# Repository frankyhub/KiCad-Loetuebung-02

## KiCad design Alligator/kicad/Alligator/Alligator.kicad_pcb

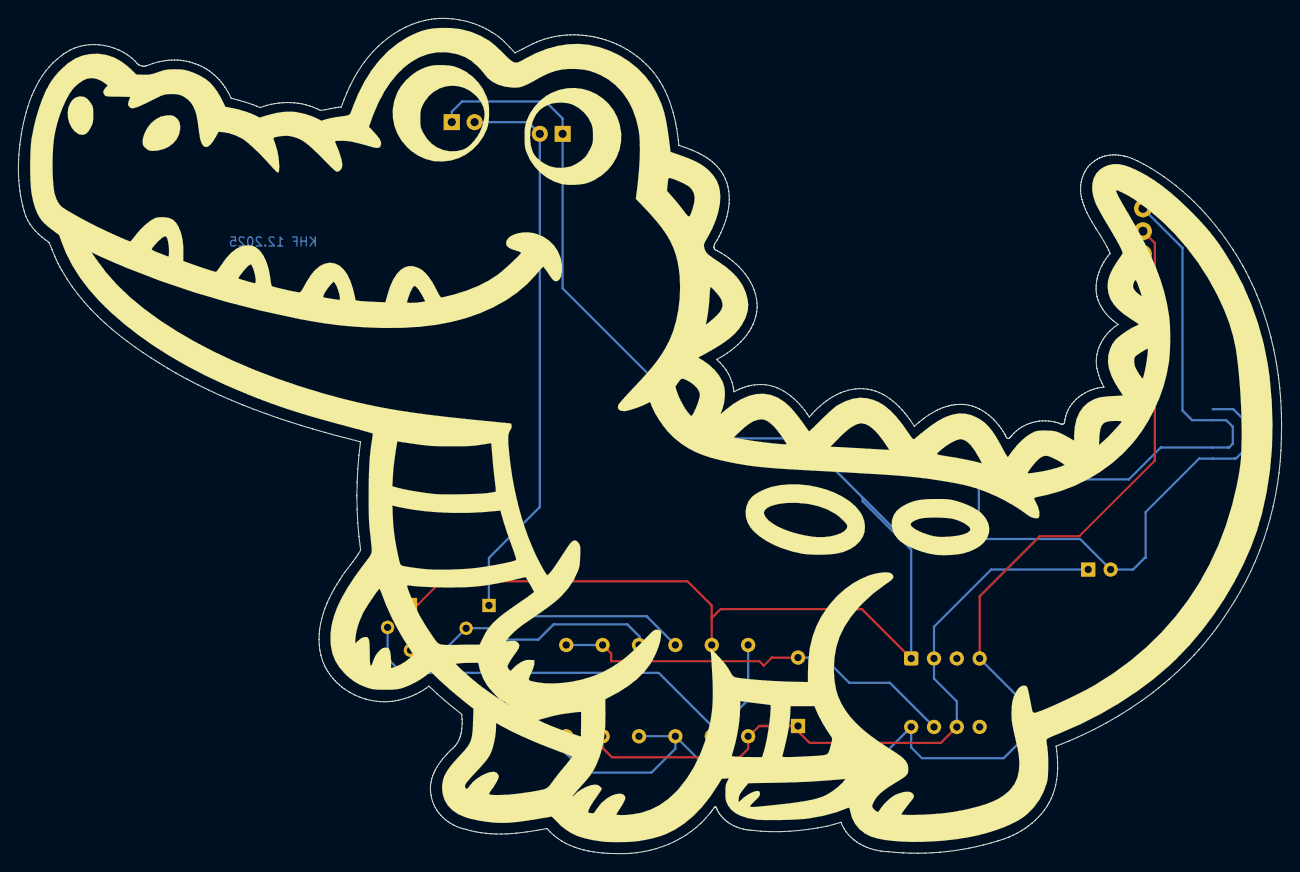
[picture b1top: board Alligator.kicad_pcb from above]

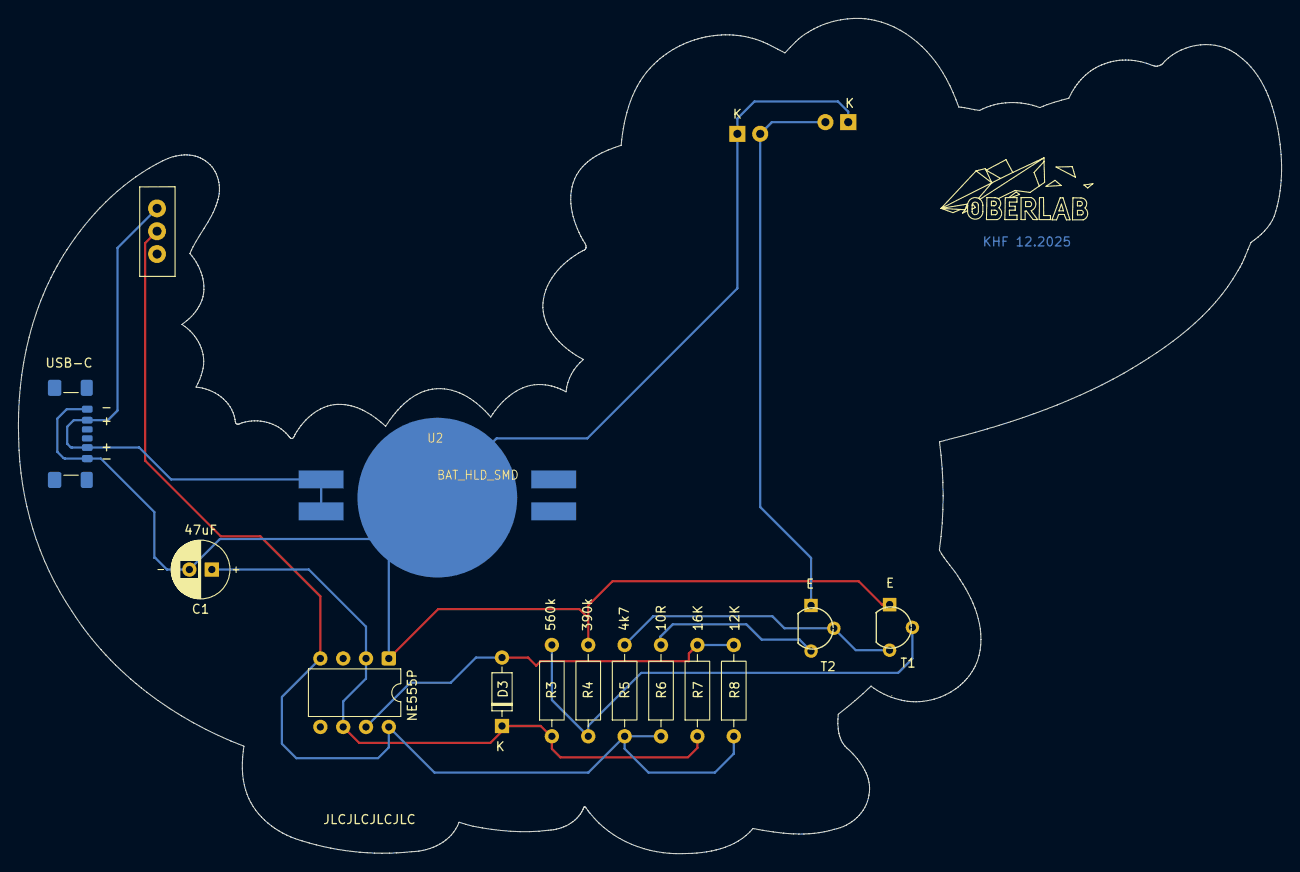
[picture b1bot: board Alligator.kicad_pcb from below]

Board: 2 copper layers, 140.6 x 93.0 mm, 16 parts (14 on the bottom side), 9 nets.

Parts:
C1: 47uF; C_Radial_D6.3mm_P2.50mm
D1, D2: LED; LED_D3.0mm
D3: 1N4148; 1N4147_P7.62mm_Horizontal
Q1, Q2: Q_NPN_EBC; TO-92L_Wide
R3: 560k; R_Axial_DIN0207_L6.3mm_D2.5mm_P10.16mm_Horizontal
R4: 390k; R_Axial_DIN0207_L6.3mm_D2.5mm_P10.16mm_Horizontal
R5: 4k7; R_Axial_DIN0207_L6.3mm_D2.5mm_P10.16mm_Horizontal
R6: 10R; R_Axial_DIN0207_L6.3mm_D2.5mm_P10.16mm_Horizontal
R7: 16K; R_Axial_DIN0207_L6.3mm_D2.5mm_P10.16mm_Horizontal
R8: 12K; R_Axial_DIN0207_L6.3mm_D2.5mm_P10.16mm_Horizontal
S1: Micro_Schalter; Micro_SchalterKHF
U1: NE555P; DIP-8_W7.62mm
U2: BAT_HLD_SMD; BAT-HLD-SMD-Blech
USB-C: USB_C_Receptacle_GCT_USB4135-GF-A_6P_TopMnt_Horiz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; USB_C_Receptacle_GCT_USB4135-GF-A_6P_TopMnt_Horizontal

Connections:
unnamed: D1.2 (A), D2.2 (A), Q2.1 (E)
unnamed: C1.2, D1.1 (K), D2.1 (K), Q1.1 (E), R4.2, U1.1 (GND), U2.2, USB-C.A12, USB-C.B12
unnamed: D3.2 (A), R7.2, R8.2, U1.7 (DIS)
unnamed: C1.1, D3.1 (K), R3.1, R7.1, U1.2 (TR), U1.6 (THR)
unnamed: Q1.2 (B), R3.2, R4.1
unnamed: Q1.3 (C), Q2.2 (B), R5.2
unnamed: Q2.3 (C), R6.2
unnamed: S1.1 (A), U2.1, USB-C.A9, USB-C.B9
unnamed: R5.1, R6.1, R8.1, S1.2 (E), U1.4 (R), U1.8 (VCC)

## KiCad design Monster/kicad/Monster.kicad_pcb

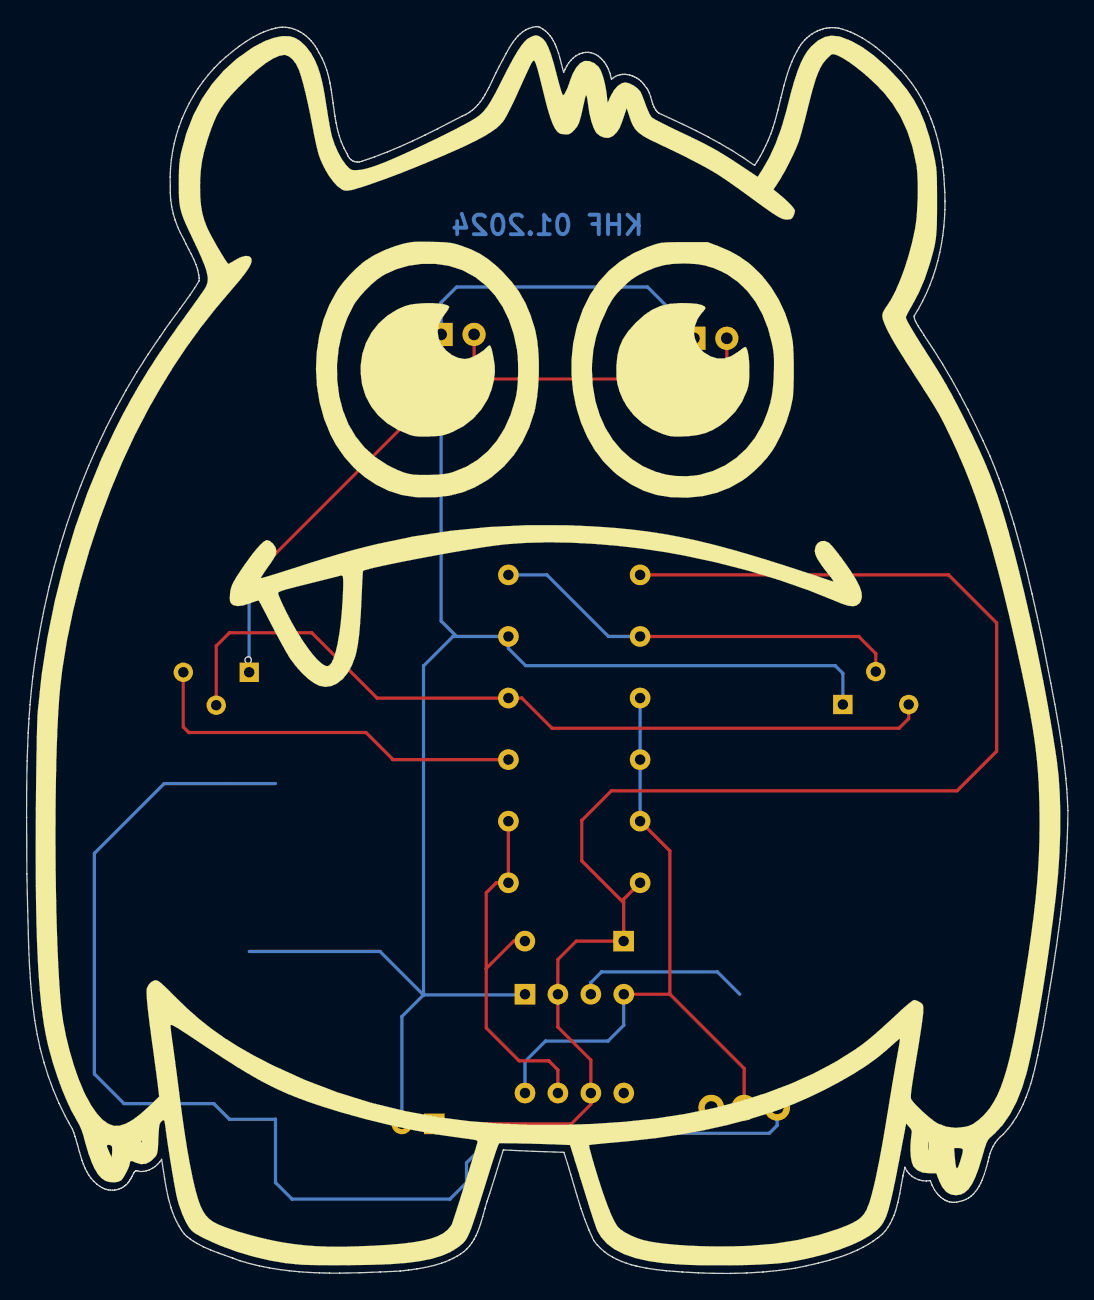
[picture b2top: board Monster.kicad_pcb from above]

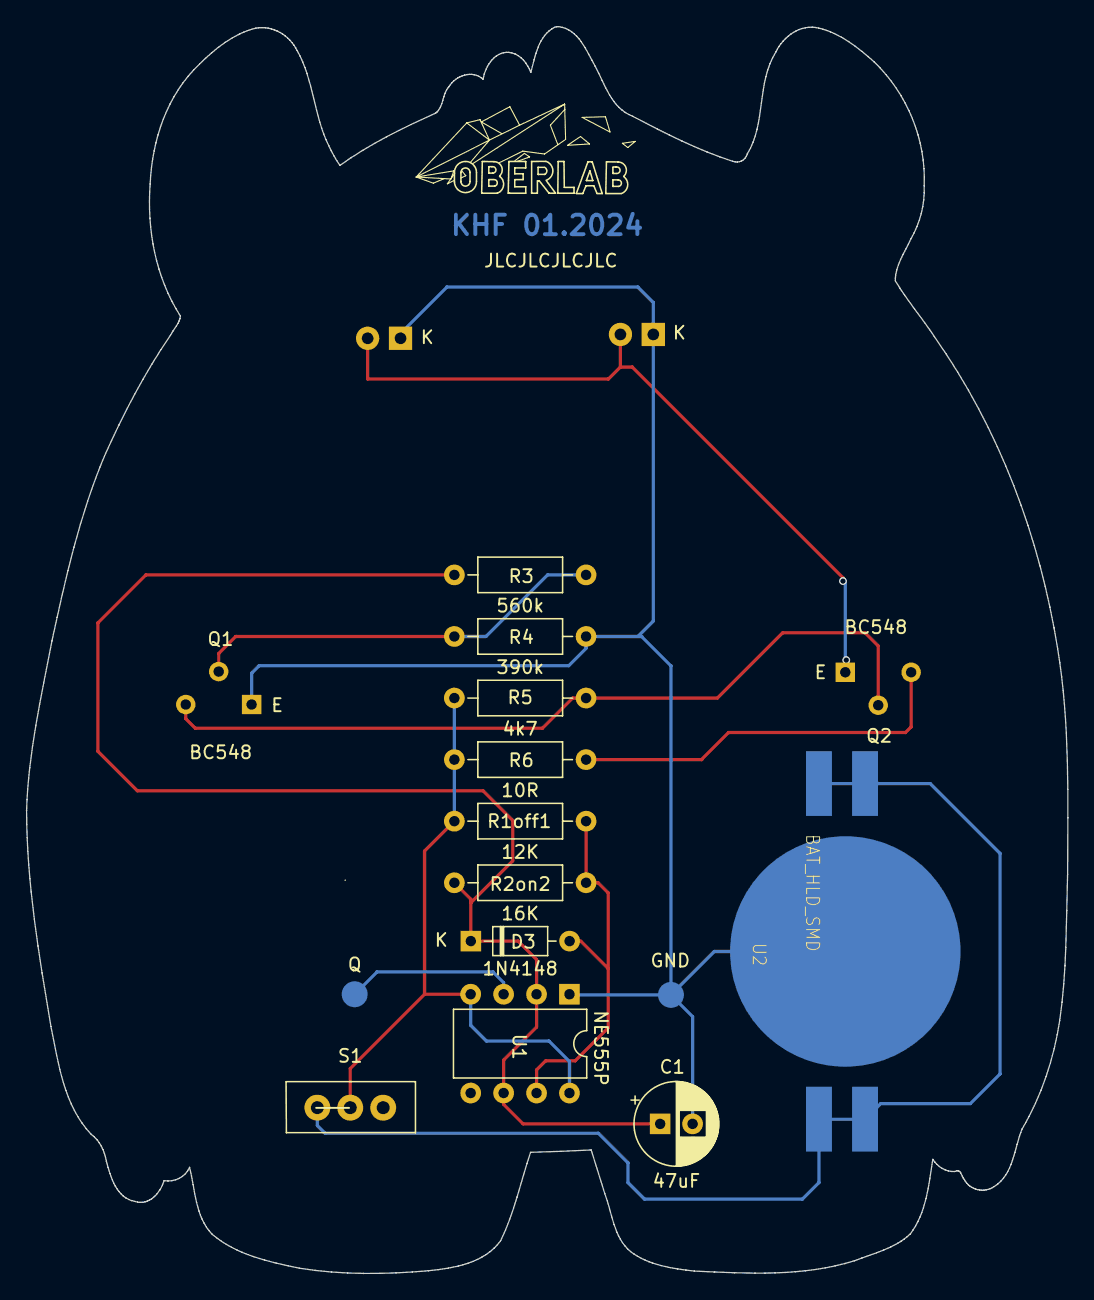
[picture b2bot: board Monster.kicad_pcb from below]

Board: 2 copper layers, 80.3 x 96.2 mm, 16 parts (14 on the bottom side), 9 nets.

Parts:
C1: 47uF; CP_Radial_D6.3mm_P2.50mm
D1, D2: LED; LED_D5.0mm
D3: 1N4148; D_DO-35_SOD27_P7.62mm_Horizontal
Q: LP_rund
Q1, Q2: BC548; TO-92L_Wide
R1off1: 12K; R_Axial_DIN0207_L6.3mm_D2.5mm_P10.16mm_Horizontal
R2on2: 16K; R_Axial_DIN0207_L6.3mm_D2.5mm_P10.16mm_Horizontal
R3: 560k; R_Axial_DIN0207_L6.3mm_D2.5mm_P10.16mm_Horizontal
R4: 390k; R_Axial_DIN0207_L6.3mm_D2.5mm_P10.16mm_Horizontal
R5: 4k7; R_Axial_DIN0207_L6.3mm_D2.5mm_P10.16mm_Horizontal
R6: 10R; R_Axial_DIN0207_L6.3mm_D2.5mm_P10.16mm_Horizontal
S1: Micro_Schalter; Micro_SchalterKHF
U1: NE555P; DIP-8_W7.62mm
U2: BAT_HLD_SMD; BAT-HLD-SMD-Blech

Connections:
unnamed: D1.2 (A), D2.2 (A), Q2.3 (C)
unnamed: C1.2, D1.1 (K), D2.1 (K), Q1.3 (C), R4.2, U1.1 (GND), U2.2
unnamed: D3.2 (A), R1off1.2, R2on2.2, U1.7 (DIS)
unnamed: C1.1, D3.1 (K), R2on2.1, R3.1, U1.2 (TR), U1.6 (THR)
unnamed: Q1.2 (B), R3.2, R4.1
unnamed: Q1.1 (E), Q2.2 (B), R5.2
unnamed: Q2.1 (E), R6.2
unnamed: S1.1 (A), U2.1
unnamed: R1off1.1, R5.1, R6.1, S1.2 (E), U1.4 (R), U1.8 (VCC)

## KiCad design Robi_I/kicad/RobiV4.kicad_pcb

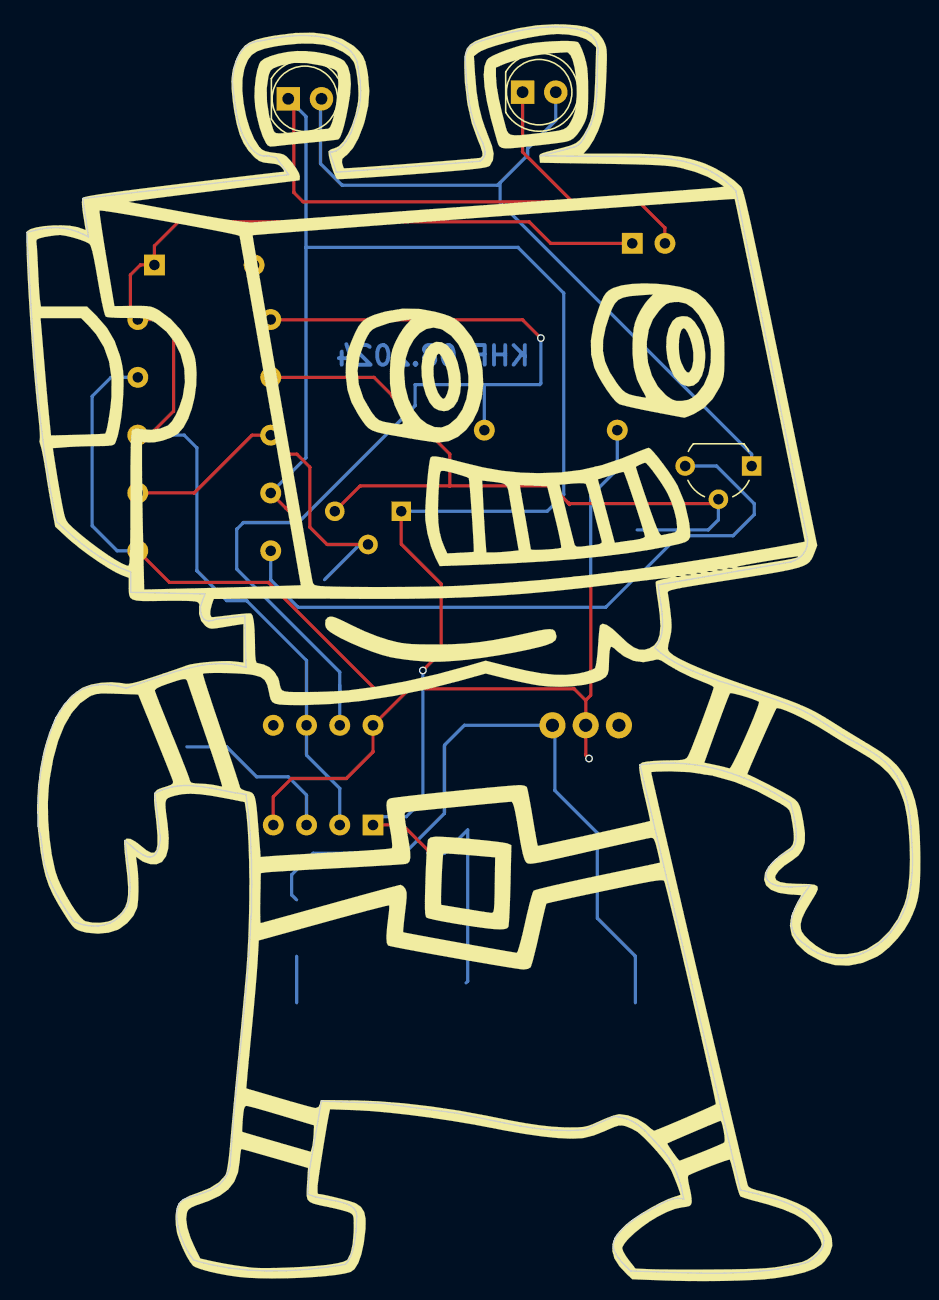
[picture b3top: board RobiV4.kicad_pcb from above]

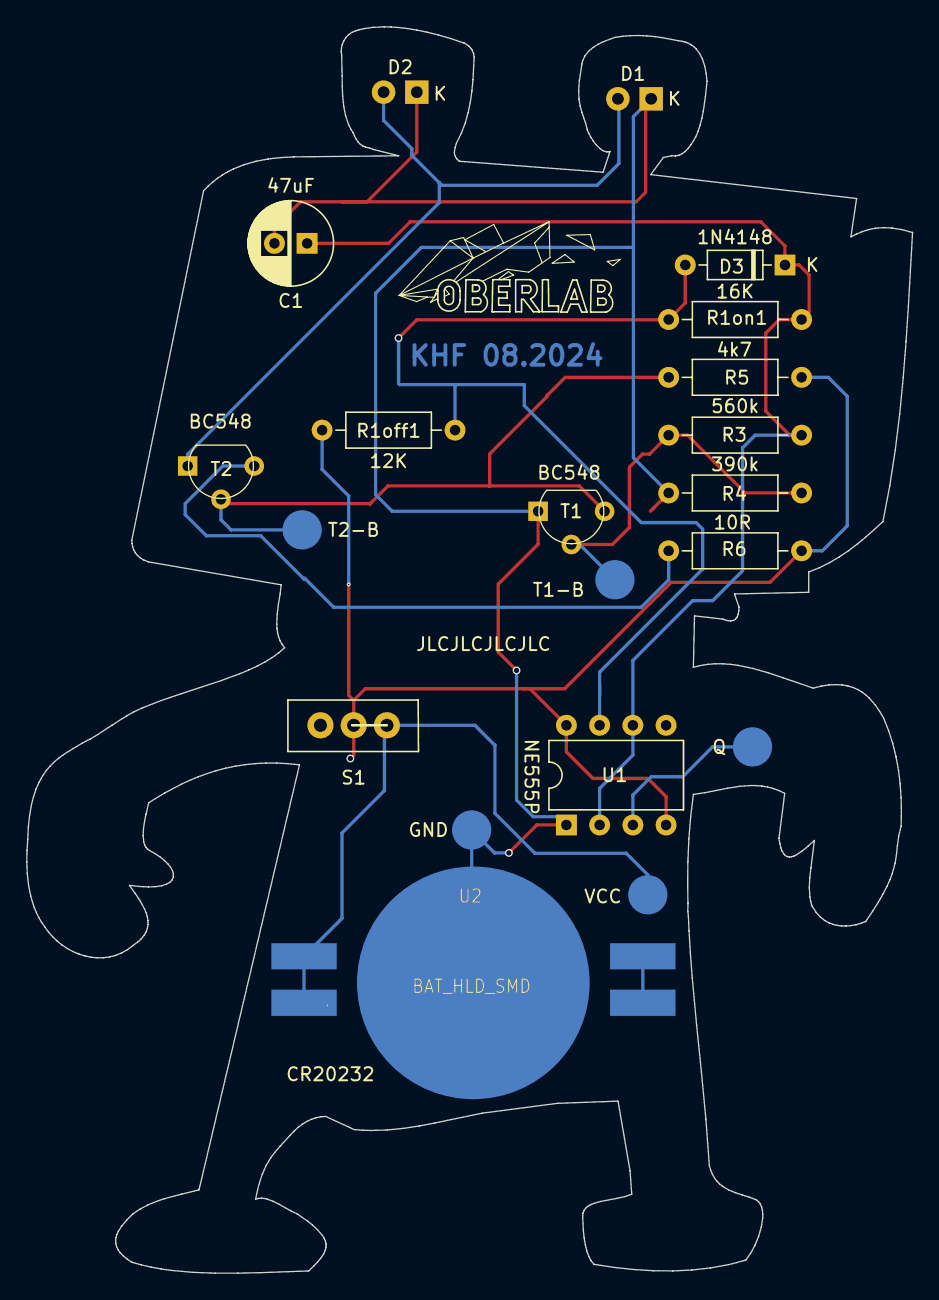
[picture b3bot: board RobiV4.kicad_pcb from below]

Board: 2 copper layers, 67.7 x 95.3 mm, 20 parts (16 on the bottom side), 9 nets.

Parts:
C1: 47uF; CP_Radial_D6.3mm_P2.50mm
D1, D2: LED; LED_D5.0mm
D3: 1N4148; D_DO-35_SOD27_P7.62mm_Horizontal
GND: LP_rund
Q: LP_rund
R1off1: 12K; R_Axial_DIN0207_L6.3mm_D2.5mm_P10.16mm_Horizontal
R1on1: 16K; R_Axial_DIN0207_L6.3mm_D2.5mm_P10.16mm_Horizontal
R3: 560k; R_Axial_DIN0207_L6.3mm_D2.5mm_P10.16mm_Horizontal
R4: 390k; R_Axial_DIN0207_L6.3mm_D2.5mm_P10.16mm_Horizontal
R5: 4k7; R_Axial_DIN0207_L6.3mm_D2.5mm_P10.16mm_Horizontal
R6: 10R; R_Axial_DIN0207_L6.3mm_D2.5mm_P10.16mm_Horizontal
S1: Micro_Schalter; Micro_SchalterKHF
T1, T2: Q_NPN_EBC; TO-92L_Wide
T1-B, T2-B: LP_rund
U1: NE555P; DIP-8_W7.62mm
U2: BAT_HLD_SMD; BAT-HLD-SMD-Blech
VCC: LP_rund

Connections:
unnamed: D1.2 (A), D2.2 (A), T2.1 (E)
unnamed: C1.2, D1.1 (K), D2.1 (K), GND.1, R4.2, T1.1 (E), U1.1 (GND), U2.2
unnamed: D3.2 (A), R1off1.2, R1on1.2, U1.7 (DIS)
unnamed: C1.1, D3.1 (K), R1on1.1, R3.1, U1.2 (TR), U1.6 (THR)
unnamed: R3.2, R4.1, T1.2 (B), T1-B.1
unnamed: R5.2, T1.3 (C), T2.2 (B), T2-B.1
unnamed: R6.2, T2.3 (C)
unnamed: S1.1 (A), U2.1
unnamed: R1off1.1, R5.1, R6.1, S1.2 (E), U1.4 (R), U1.8 (VCC)
